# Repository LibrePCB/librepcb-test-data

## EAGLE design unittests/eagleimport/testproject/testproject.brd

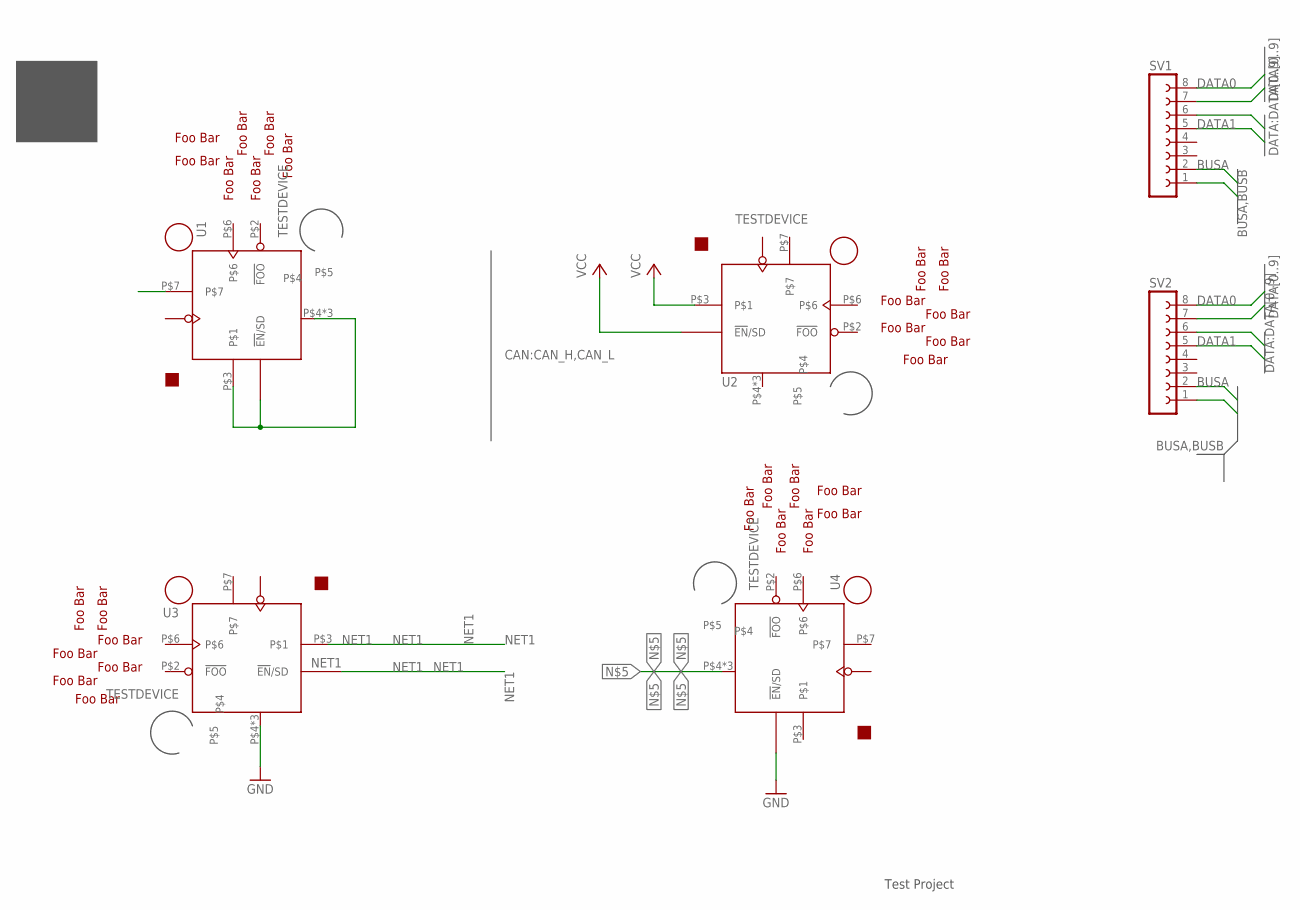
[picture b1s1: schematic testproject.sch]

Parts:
SV1, SV2: FE08-1; FE08
U1, U2, U3, U4: TESTDEVICE; TESTPACKAGE

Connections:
BUSA: SV1.2, SV2.2
BUSB: SV1.1, SV2.1
DATA0: SV1.6, SV1.8, SV2.6, SV2.8
DATA1: SV1.5, SV1.7, SV2.5, SV2.7
GND: U3.P$4, U3.P$13, U3.P$16, U4.P$1 (!EN!/SD)
unnamed: U1.P$1 (!EN!/SD), U1.P$3, U1.P$4, U1.P$13, U1.P$16
unnamed: U4.P$4, U4.P$13, U4.P$16
NET1: U3.P$1 (!EN!/SD), U3.P$3
VCC: U2.P$1 (!EN!/SD), U2.P$3

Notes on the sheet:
Test Project

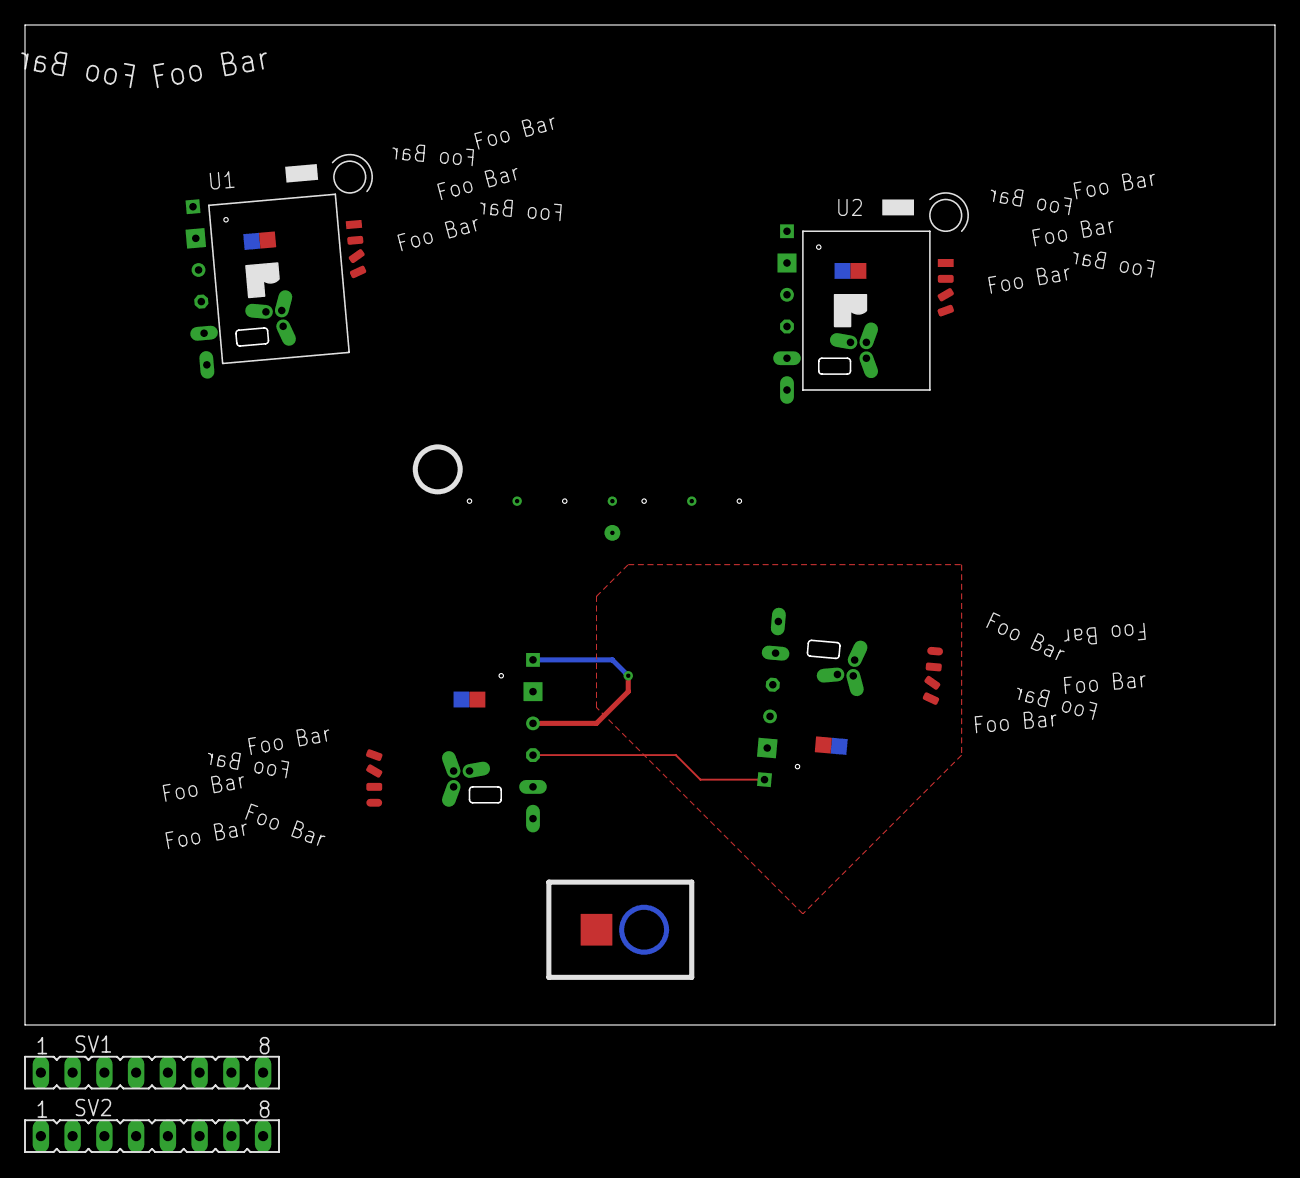
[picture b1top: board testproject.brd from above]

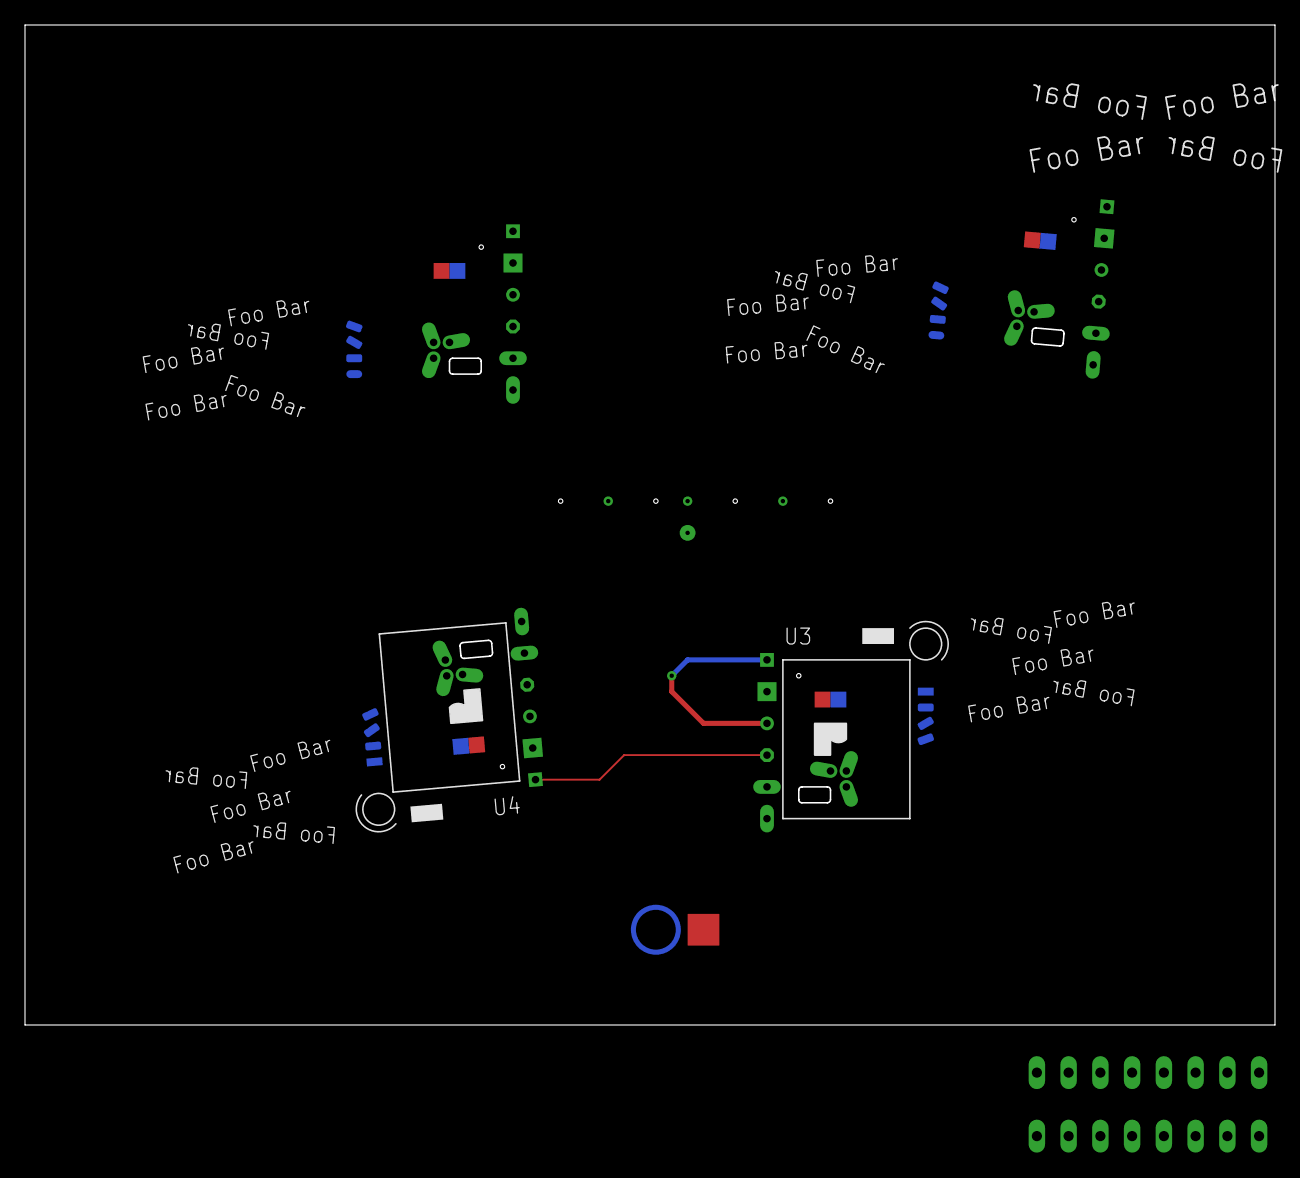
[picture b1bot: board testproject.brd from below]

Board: 2 copper layers, 100.0 x 80.0 mm, 6 parts (2 on the bottom side), 9 nets.

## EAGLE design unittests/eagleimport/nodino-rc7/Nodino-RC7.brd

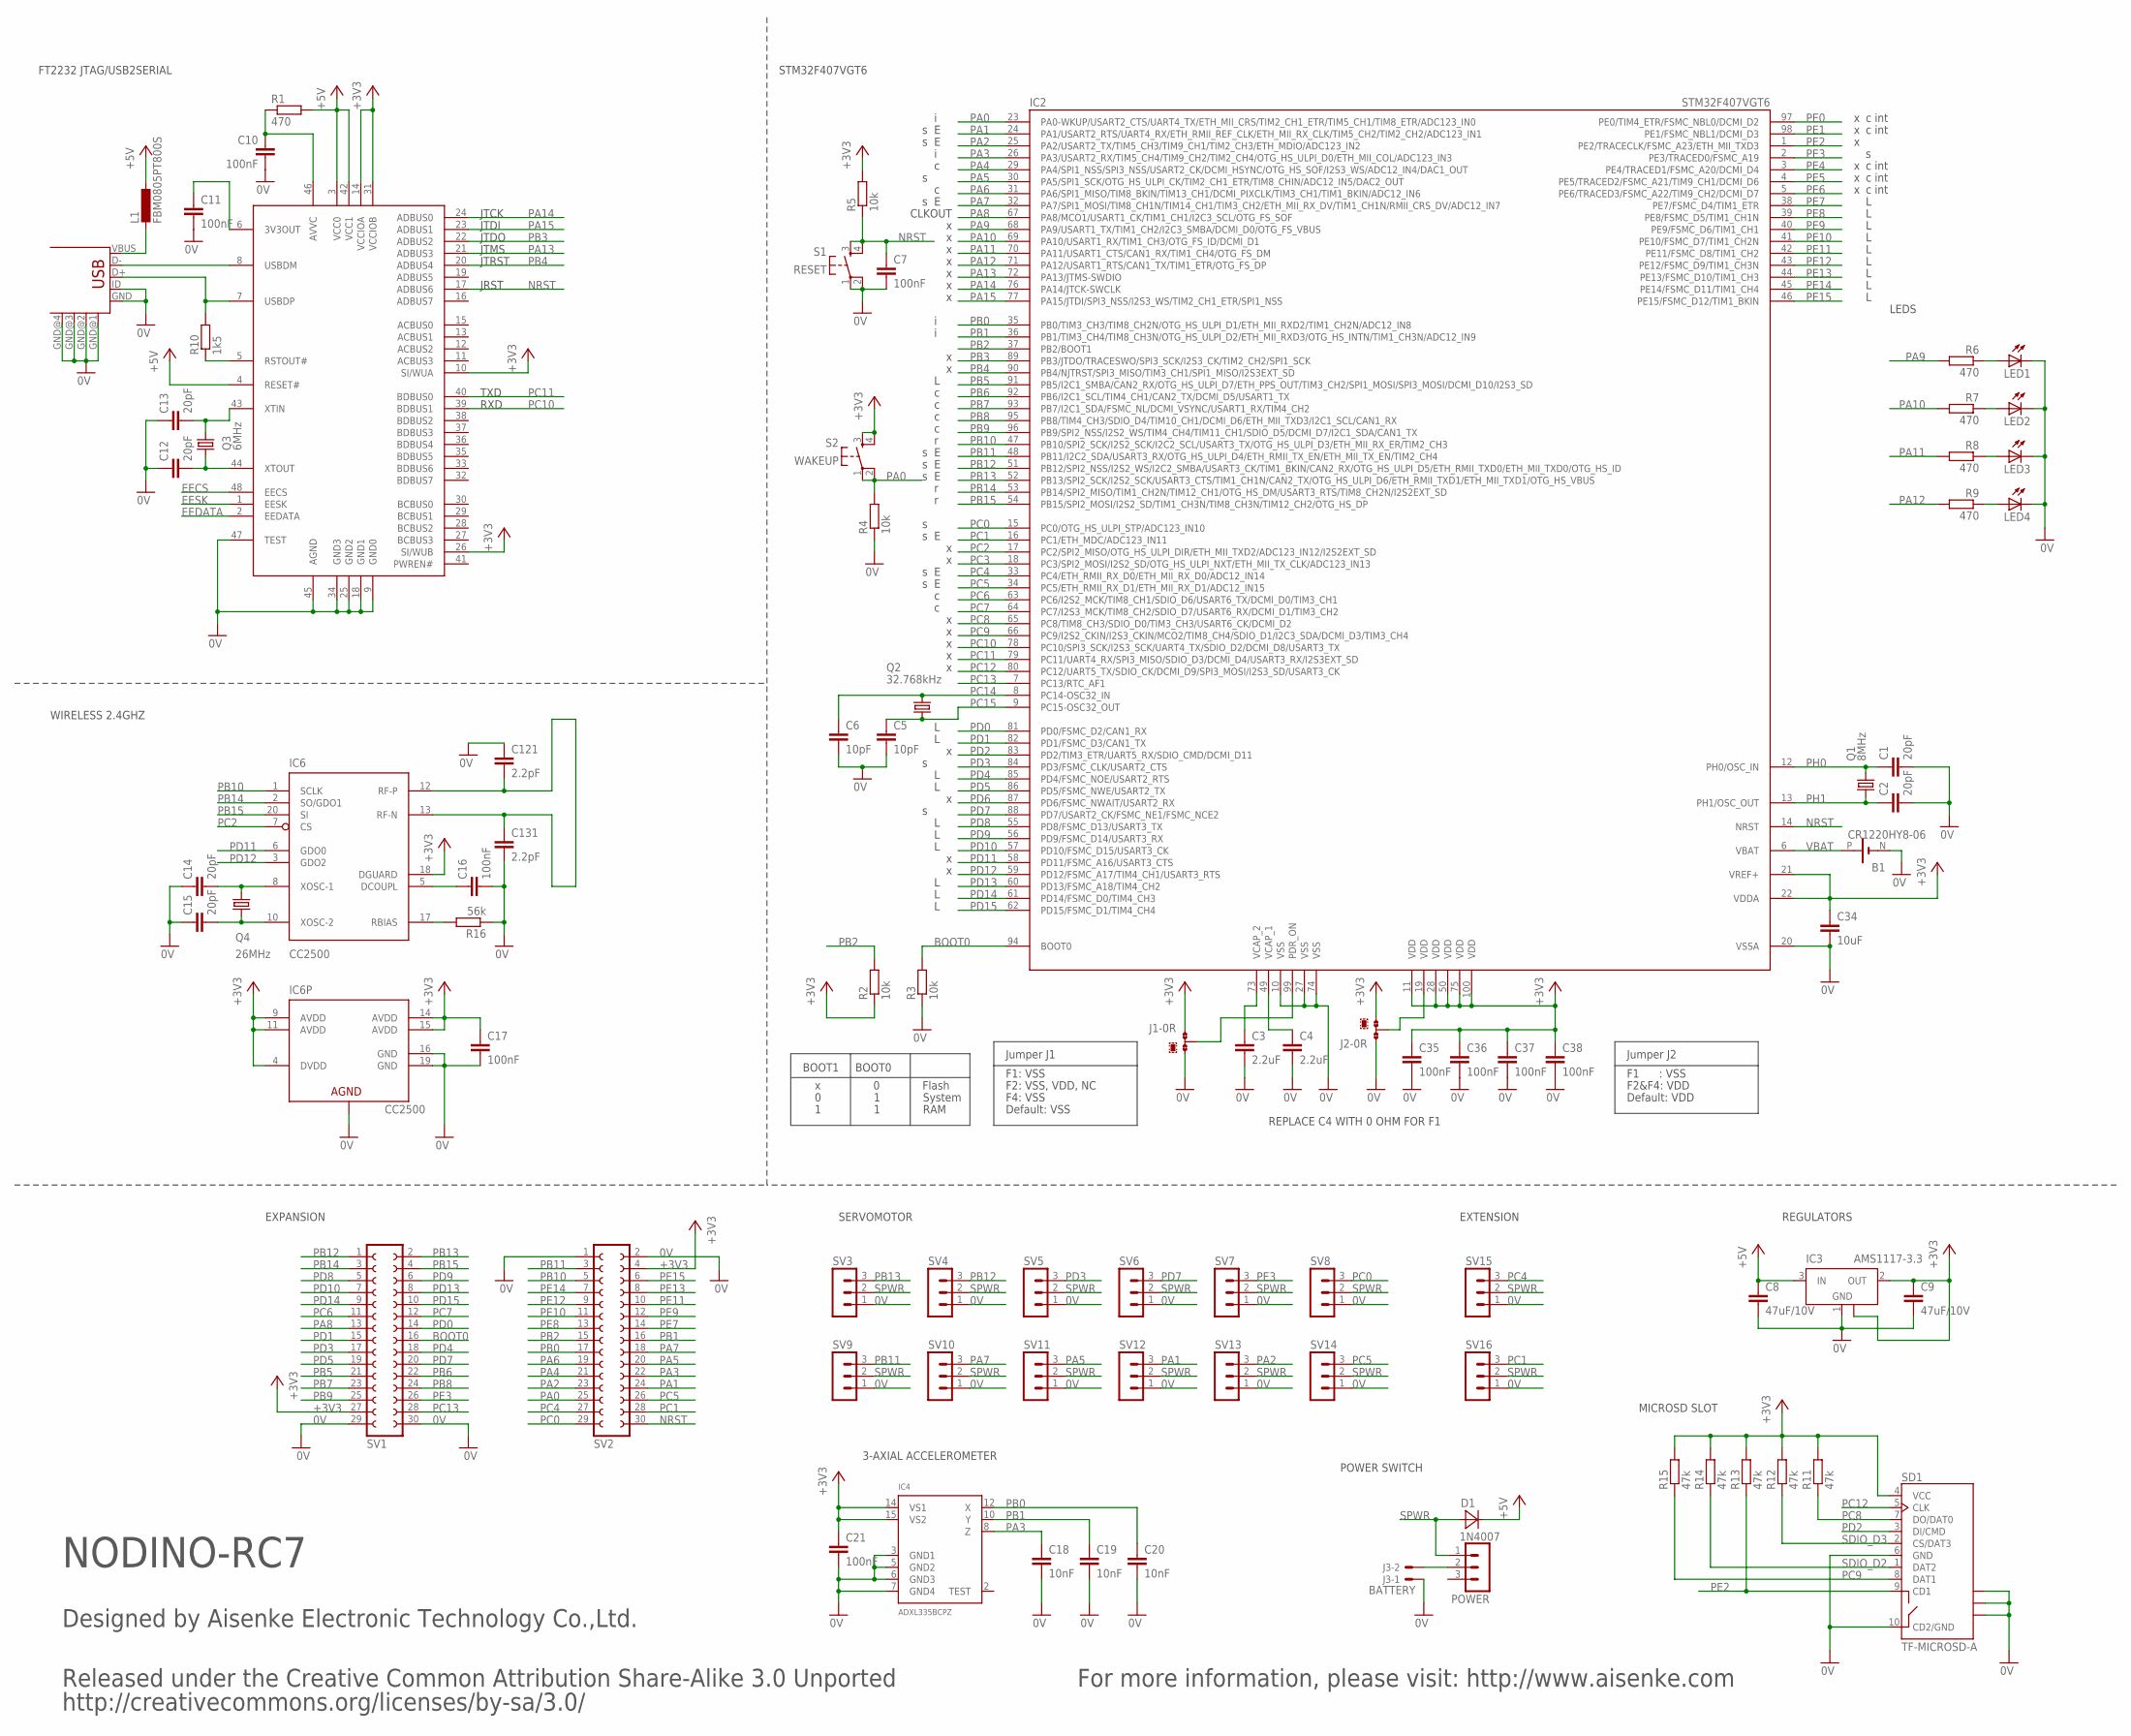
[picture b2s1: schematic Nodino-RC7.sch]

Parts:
B1: CR1220HY8-06; HY8-06
C1, C2, C12, C13, C14, C15: 20pF; C0603K
C3, C4: 2.2uF; C0603K
C5, C6: 10pF; C0603K
C7, C10, C11, C16, C17, C21, C35, C36, C37, C38: 100nF; C0603K
C8, C9: 47uF/10V; C3225
C18, C19, C20: 10nF; C0603K
C34: 10uF; C0603K
C121, C131: 2.2pF; C0603K
D1: 1N4007; DO214AC
IC1: FT2232D; LQFP48
IC2: STM32F407VGT6; LQFP100
IC3: AMS1117-3.3; SOT223
IC4: ADXL335BCPZ; LFCSP16-W
IC6: CC2500; QLP-20
J1, J2: 0R-JUMPA0603; A0R-JMP0603K
J3: BATTERY; 6410-02
L1: FBM0805PT800S; L0805
LED1, LED2, LED3, LED4: LEDCHIP-LED0805; CHIP-LED0805
POWER: MA03-1
Q1: 8MHz; CSM-7X-DU
Q2: 32.768kHz; MC-306
Q3: 6MHz; CSM-7X-DU
Q4: 26MHz; CSM-7X-DU
R1, R6, R7, R8, R9: 470; R0603K
R2, R3, R4, R5: 10k; R0603K
R10: 1k5; R0603K
R11, R12, R13, R14, R15: 47k; R0603K
R16: 56k; R0603K
S1: RESET; ALCOSWITCH-SMD
S2: WAKEUP; ALCOSWITCH-SMD
SD1: TF-MICROSD-A; MICROSD/CD
SV1, SV2: FE15-2
SV3, SV4, SV5, SV6, SV7, SV8, SV9, SV10, SV11, SV12, SV13, SV14, SV15, SV16: MA03-1
USB1: USB-SHIELD; USB-M-S1

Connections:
0V: B1.N (-), C1.2, C2.2, C3.2, C4.2, C5.2, C6.2, C7.2, C8.2, C9.2, C10.2, C11.2, C12.1, C13.1, C14.1, C15.1, C16.2, C17.2, C18.2, C19.2, C20.2, C21.2, C34.2, C35.2, C36.2, C37.2, C38.2, C121.1, C131.2, IC1.9 (GND0), IC1.18 (GND1), IC1.25 (GND2), IC1.34 (GND3), IC1.45 (AGND), IC1.47 (TEST), IC2.10 (VSS), IC2.20 (VSSA), IC2.27 (VSS), IC2.74 (VSS), IC3.1 (GND), IC4.3 (GND1), IC4.5 (GND2), IC4.6 (GND3), IC4.7 (GND4), IC6.16 (GND), IC6.19 (GND), IC6.21 (AGND), J1.1, J2.3, J3.1, LED1.C, LED2.C, LED3.C, LED4.C, R3.1, R4.1, R16.1, S1.1, S1.2 (P1), SD1.6 (GND), SD1.10 (CD2/GND), SD1.11 (GND), SD1.12 (GND), SD1.13 (GND), SV1.29, SV1.30, SV2.1, SV2.2, SV3.1, SV4.1, SV5.1, SV6.1, SV7.1, SV8.1, SV9.1, SV10.1, SV11.1, SV12.1, SV13.1, SV14.1, SV15.1, SV16.1, USB1.GND, USB1.GND@1 (GND), USB1.GND@2 (GND), USB1.GND@3 (GND), USB1.GND@4 (GND), USB1.ID
+3V3: C9.1, C17.1, C21.1, C34.1, C35.1, C36.1, C37.1, C38.1, IC1.10 (SI/WUA), IC1.14 (VCCIOA), IC1.26 (SI/WUB), IC1.31 (VCCIOB), IC2.11 (VDD), IC2.21 (VREF+), IC2.22 (VDDA), IC2.28 (VDD), IC2.50 (VDD), IC2.75 (VDD), IC2.100 (VDD), IC3.2 (OUT), IC3.4 (GND), IC4.14 (VS1), IC4.15 (VS2), IC6.4 (DVDD), IC6.9 (AVDD), IC6.11 (AVDD), IC6.14 (AVDD), IC6.15 (AVDD), IC6.18 (DGUARD), J1.3, J2.1, R2.1, R5.2, R11.2, R12.2, R13.2, R14.2, R15.2, S2.3 (S), S2.4 (S1), SD1.4 (VCC), SV1.27, SV2.4
+5V: C8.1, D1.C, IC1.3 (VCC0), IC1.4 (RESET#), IC1.42 (VCC1), IC3.3 (IN), L1.1, R1.2
BOOT0: IC2.94 (BOOT0), R3.2, SV1.16
DCOUPL: C16.1, IC6.5 (DCOUPL)
EECS: IC1.48 (EECS)
EEDATA: IC1.2 (EEDATA)
EESK: IC1.1 (EESK)
FOLDED_DIPOLE_ANTENNA: C121.2, C131.1, IC6.12 (RF-P), IC6.13 (RF-N)
unnamed: C15.2, IC6.10 (XOSC-2), Q4.1
unnamed: C3.1, IC2.73 (VCAP_2)
unnamed: C14.2, IC6.8 (XOSC-1), Q4.2
unnamed: C4.1, IC2.49 (VCAP_1)
unnamed: IC1.8 (USBDM), USB1.D-
unnamed: IC2.99 (PDR_ON), J1.2
unnamed: LED1.A, R6.1
unnamed: LED2.A, R7.1
unnamed: LED3.A, R8.1
unnamed: LED4.A, R9.1
unnamed: IC1.7 (USBDP), R10.2, USB1.D+
unnamed: L1.2, USB1.VBUS
unnamed: IC1.5 (RSTOUT#), R10.1
unnamed: C10.1, IC1.46 (AVVC), R1.1
unnamed: C11.1, IC1.6 (3V3OUT)
unnamed: C12.2, IC1.44 (XTOUT), Q3.1
unnamed: C13.2, IC1.43 (XTIN), Q3.2
unnamed: IC6.17 (RBIAS), R16.2
unnamed: IC2.19 (VDD), J2.2
unnamed: J3.2, POWER.2
NRST: C7.1, IC1.17 (ADBUS6), IC2.14 (NRST), R5.1, S1.3 (S), S1.4 (S1), SV2.30
PA0: IC2.23 (PA0-WKUP/USART2_CTS/UART4_TX/ETH_MII_CR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), R4.2, S2.1, S2.2 (P1), SV2.25
PA1: IC2.24 (PA1/USART2_RTS/UART4_RX/ETH_RMII_REF_CL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), SV2.24, SV12.3
PA2: IC2.25 (PA2/USART2_TX/TIM5_CH3/TIM9_CH1/TIM2_CH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), SV2.23, SV13.3
PA3: C18.1, IC2.26 (PA3/USART2_RX/TIM5_CH4/TIM9_CH2/TIM2_CH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), IC4.8 (Z), SV2.22
PA4: IC2.29 (PA4/SPI1_NSS/SPI3_NSS/USART2_CK/DCMI_HS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), SV2.21
PA5: IC2.30 (PA5/SPI1_SCK/OTG_HS_ULPI_CK/TIM2_CH1_ET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), SV2.20, SV11.3
PA6: IC2.31 (PA6/SPI1_MISO/TIM8_BKIN/TIM13_CH1/DCMI_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), SV2.19
PA7: IC2.32 (PA7/SPI1_MOSI/TIM8_CH1N/TIM14_CH1/TIM3_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), SV2.18, SV10.3
PA8: IC2.67 (PA8/MCO1/USART1_CK/TIM1_CH1/I2C3_SCL/OT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), SV1.13
PA9: IC2.68 (PA9/USART1_TX/TIM1_CH2/I2C3_SMBA/DCMI_D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), R6.2
PA10: IC2.69 (PA10/USART1_RX/TIM1_CH3/OTG_FS_ID/DCMI_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), R7.2
PA11: IC2.70 (PA11/USART1_CTS/CAN1_RX/TIM1_CH4/OTG_FS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), R8.2
PA12: IC2.71 (PA12/USART1_RTS/CAN1_TX/TIM1_ETR/OTG_FS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), R9.2
PA13: IC1.21 (ADBUS3), IC2.72 (PA13/JTMS-SWDIO)
PA14: IC1.24 (ADBUS0), IC2.76 (PA14/JTCK-SWCLK)
PA15: IC1.23 (ADBUS1), IC2.77 (PA15/JTDI/SPI3_NSS/I2S3_WS/TIM2_CH1_ETR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)
PB0: C20.1, IC2.35 (PB0/TIM3_CH3/TIM8_CH2N/OTG_HS_ULPI_D1/E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), IC4.12 (X), SV2.17
PB1: C19.1, IC2.36 (PB1/TIM3_CH4/TIM8_CH3N/OTG_HS_ULPI_D2/E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), IC4.10 (Y), SV2.16
PB2: IC2.37 (PB2/BOOT1), R2.2, SV2.15
PB3: IC1.22 (ADBUS2), IC2.89 (PB3/JTDO/TRACESWO/SPI3_SCK/I2S3_CK/TIM2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)
PB4: IC1.20 (ADBUS4), IC2.90 (PB4/NJTRST/SPI3_MISO/TIM3_CH1/SPI1_MISO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)
PB5: IC2.91 (PB5/I2C1_SMBA/CAN2_RX/OTG_HS_ULPI_D7/ET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), SV1.21
PB6: IC2.92 (PB6/I2C1_SCL/TIM4_CH1/CAN2_TX/DCMI_D5/U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), SV1.22
PB7: IC2.93 (PB7/I2C1_SDA/FSMC_NL/DCMI_VSYNC/USART1_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), SV1.23
PB8: IC2.95 (PB8/TIM4_CH3/SDIO_D4/TIM10_CH1/DCMI_D6/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), SV1.24
PB9: IC2.96 (PB9/SPI2_NSS/I2S2_WS/TIM4_CH4/TIM11_CH1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), SV1.25
PB10: IC2.47 (PB10/SPI2_SCK/I2S2_SCK/I2C2_SCL/USART3_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), IC6.1 (SCLK), SV2.5
PB11: IC2.48 (PB11/I2C2_SDA/USART3_RX/OTG_HS_ULPI_D4/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), SV2.3, SV9.3
PB12: IC2.51 (PB12/SPI2_NSS/I2S2_WS/I2C2_SMBA/USART3_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), SV1.1, SV4.3
PB13: IC2.52 (PB13/SPI2_SCK/I2S2_SCK/USART3_CTS/TIM1_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), SV1.2, SV3.3
PB14: IC2.53 (PB14/SPI2_MISO/TIM1_CH2N/TIM12_CH1/OTG_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), IC6.2 (SO/GDO1), SV1.3
PB15: IC2.54 (PB15/SPI2_MOSI/I2S2_SD/TIM1_CH3N/TIM8_C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), IC6.20 (SI), SV1.4
PC0: IC2.15 (PC0/OTG_HS_ULPI_STP/ADC123_IN10), SV2.29, SV8.3
PC1: IC2.16 (PC1/ETH_MDC/ADC123_IN11), SV2.28, SV16.3
PC2: IC2.17 (PC2/SPI2_MISO/OTG_HS_ULPI_DIR/ETH_MII_T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), IC6.7 (CS)
PC3: IC2.18 (PC3/SPI2_MOSI/I2S2_SD/OTG_HS_ULPI_NXT/E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)
PC4: IC2.33 (PC4/ETH_RMII_RX_D0/ETH_MII_RX_D0/ADC12_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), SV2.27, SV15.3
PC5: IC2.34 (PC5/ETH_RMII_RX_D1/ETH_MII_RX_D1/ADC12_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), SV2.26, SV14.3
PC6: IC2.63 (PC6/I2S2_MCK/TIM8_CH1/SDIO_D6/USART6_TX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), SV1.11
PC7: IC2.64 (PC7/I2S3_MCK/TIM8_CH2/SDIO_D7/USART6_RX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), SV1.12
PC8: IC2.65 (PC8/TIM8_CH3/SDIO_D0/TIM3_CH3/USART6_CK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), R11.1, SD1.7 (DO/DAT0)
PC9: IC2.66 (PC9/I2S2_CKIN/I2S3_CKIN/MCO2/TIM8_CH4/S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), R15.1, SD1.8 (DAT1)
PC10: IC1.39 (BDBUS1), IC2.78 (PC10/SPI3_SCK/I2S3_SCK/UART4_TX/SDIO_D2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)
PC11: IC1.40 (BDBUS0), IC2.79 (PC11/UART4_RX/SPI3_MISO/SDIO_D3/DCMI_D4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)
PC12: IC2.80 (PC12/UART5_TX/SDIO_CK/DCMI_D9/SPI3_MOSI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), SD1.5 (CLK)
PC13: IC2.7 (PC13/RTC_AF1), SV1.28
PC14: C6.1, IC2.8 (PC14-OSC32_IN), Q2.4 (2)
PC15: C5.1, IC2.9 (PC15-OSC32_OUT), Q2.1
PD0: IC2.81 (PD0/FSMC_D2/CAN1_RX), SV1.14
PD1: IC2.82 (PD1/FSMC_D3/CAN1_TX), SV1.15
PD2: IC2.83 (PD2/TIM3_ETR/UART5_RX/SDIO_CMD/DCMI_D11), SD1.3 (DI/CMD)
PD3: IC2.84 (PD3/FSMC_CLK/USART2_CTS), SV1.17, SV5.3
PD4: IC2.85 (PD4/FSMC_NOE/USART2_RTS), SV1.18
PD5: IC2.86 (PD5/FSMC_NWE/USART2_TX), SV1.19
PD6: IC2.87 (PD6/FSMC_NWAIT/USART2_RX)
PD7: IC2.88 (PD7/USART2_CK/FSMC_NE1/FSMC_NCE2), SV1.20, SV6.3
PD8: IC2.55 (PD8/FSMC_D13/USART3_TX), SV1.5
PD9: IC2.56 (PD9/FSMC_D14/USART3_RX), SV1.6
PD10: IC2.57 (PD10/FSMC_D15/USART3_CK), SV1.7
PD11: IC2.58 (PD11/FSMC_A16/USART3_CTS), IC6.6 (GDO0)
PD12: IC2.59 (PD12/FSMC_A17/TIM4_CH1/USART3_RTS), IC6.3 (GDO2)
PD13: IC2.60 (PD13/FSMC_A18/TIM4_CH2), SV1.8
PD14: IC2.61 (PD14/FSMC_D0/TIM4_CH3), SV1.9
PD15: IC2.62 (PD15/FSMC_D1/TIM4_CH4), SV1.10
PE0: IC2.97 (PE0/TIM4_ETR/FSMC_NBL0/DCMI_D2)
PE1: IC2.98 (PE1/FSMC_NBL1/DCMI_D3)
PE2: IC2.1 (PE2/TRACECLK/FSMC_A23/ETH_MII_TXD3), R13.1, SD1.9 (CD1)
PE3: IC2.2 (PE3/TRACED0/FSMC_A19), SV1.26, SV7.3
PE4: IC2.3 (PE4/TRACED1/FSMC_A20/DCMI_D4)
PE5: IC2.4 (PE5/TRACED2/FSMC_A21/TIM9_CH1/DCMI_D6)
PE6: IC2.5 (PE6/TRACED3/FSMC_A22/TIM9_CH2/DCMI_D7)
PE7: IC2.38 (PE7/FSMC_D4/TIM1_ETR), SV2.14
PE8: IC2.39 (PE8/FSMC_D5/TIM1_CH1N), SV2.13
PE9: IC2.40 (PE9/FSMC_D6/TIM1_CH1), SV2.12
PE10: IC2.41 (PE10/FSMC_D7/TIM1_CH2N), SV2.11
PE11: IC2.42 (PE11/FSMC_D8/TIM1_CH2), SV2.10
PE12: IC2.43 (PE12/FSMC_D9/TIM1_CH3N), SV2.9
PE13: IC2.44 (PE13/FSMC_D10/TIM1_CH3), SV2.8
PE14: IC2.45 (PE14/FSMC_D11/TIM1_CH4), SV2.7
PE15: IC2.46 (PE15/FSMC_D12/TIM1_BKIN), SV2.6
PH0: C1.1, IC2.12 (PH0/OSC_IN), Q1.2
PH1: C2.1, IC2.13 (PH1/OSC_OUT), Q1.1
SDIO_D2: R14.1, SD1.1 (DAT2)
SDIO_D3: R12.1, SD1.2 (CS/DAT3)
SPWR: D1.A, POWER.1, SV3.2, SV4.2, SV5.2, SV6.2, SV7.2, SV8.2, SV9.2, SV10.2, SV11.2, SV12.2, SV13.2, SV14.2, SV15.2, SV16.2
VBAT: B1.P (+), IC2.6 (VBAT)

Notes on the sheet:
F2: VSS, VDD, NC
F4: VSS
BOOT1 BOOT0
x 0 Flash
0 1 System
1 1 RAM
Default: VSS
STM32F407VGT6
FT2232 JTAG/USB2SERIAL
REGULATORS
MICROSD SLOT
LEDS
NODINO-RC7
Designed by Aisenke Electronic Technology Co.,Ltd.
Released under the Creative Common Attribution Share-Alike 3.0 Unported
http://creativecommons.org/licenses/by-sa/3.0/
For more information, please visit: http://www.aisenke.com
Jumper J1
RXD
TXD
JRST
JTRST
JTMS
JTDO
JTDI
JTCK
F1 : VSS
F2&F4: VDD
Default: VDD
Jumper J2
F1: VSS
REPLACE C4 WITH 0 OHM FOR F1
WIRELESS 2.4GHZ
EXPANSION
3-AXIAL ACCELEROMETER
c int
CLKOUT
SERVOMOTOR
EXTENSION
POWER SWITCH

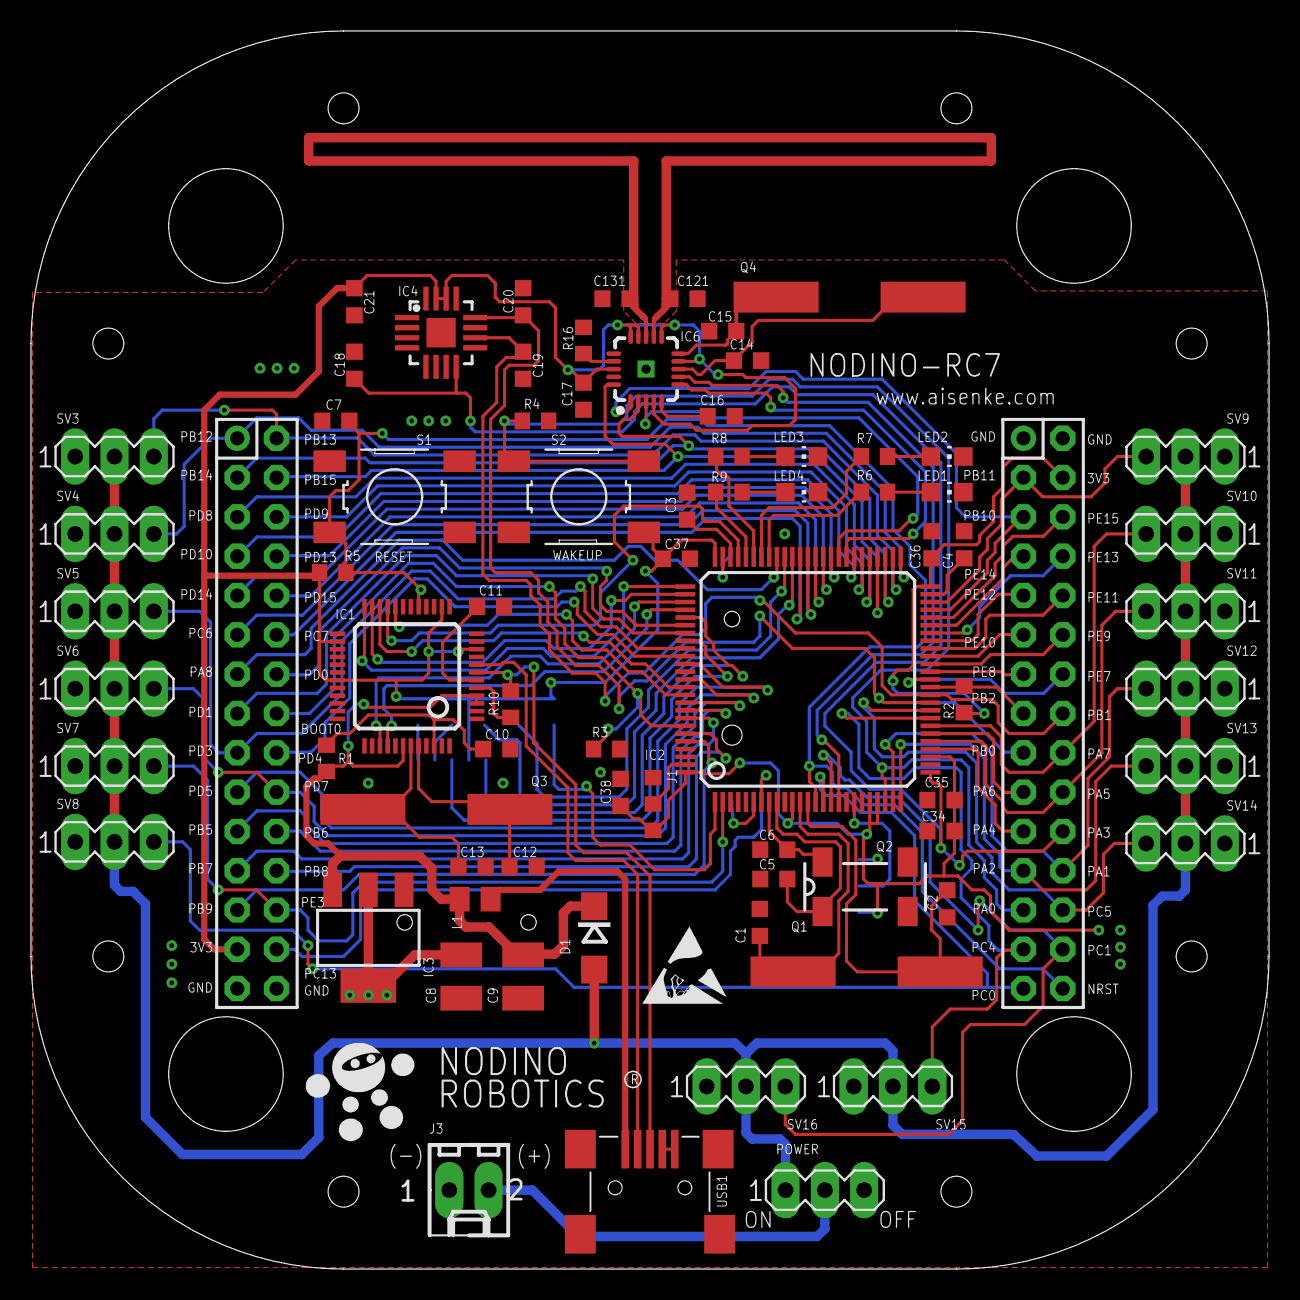
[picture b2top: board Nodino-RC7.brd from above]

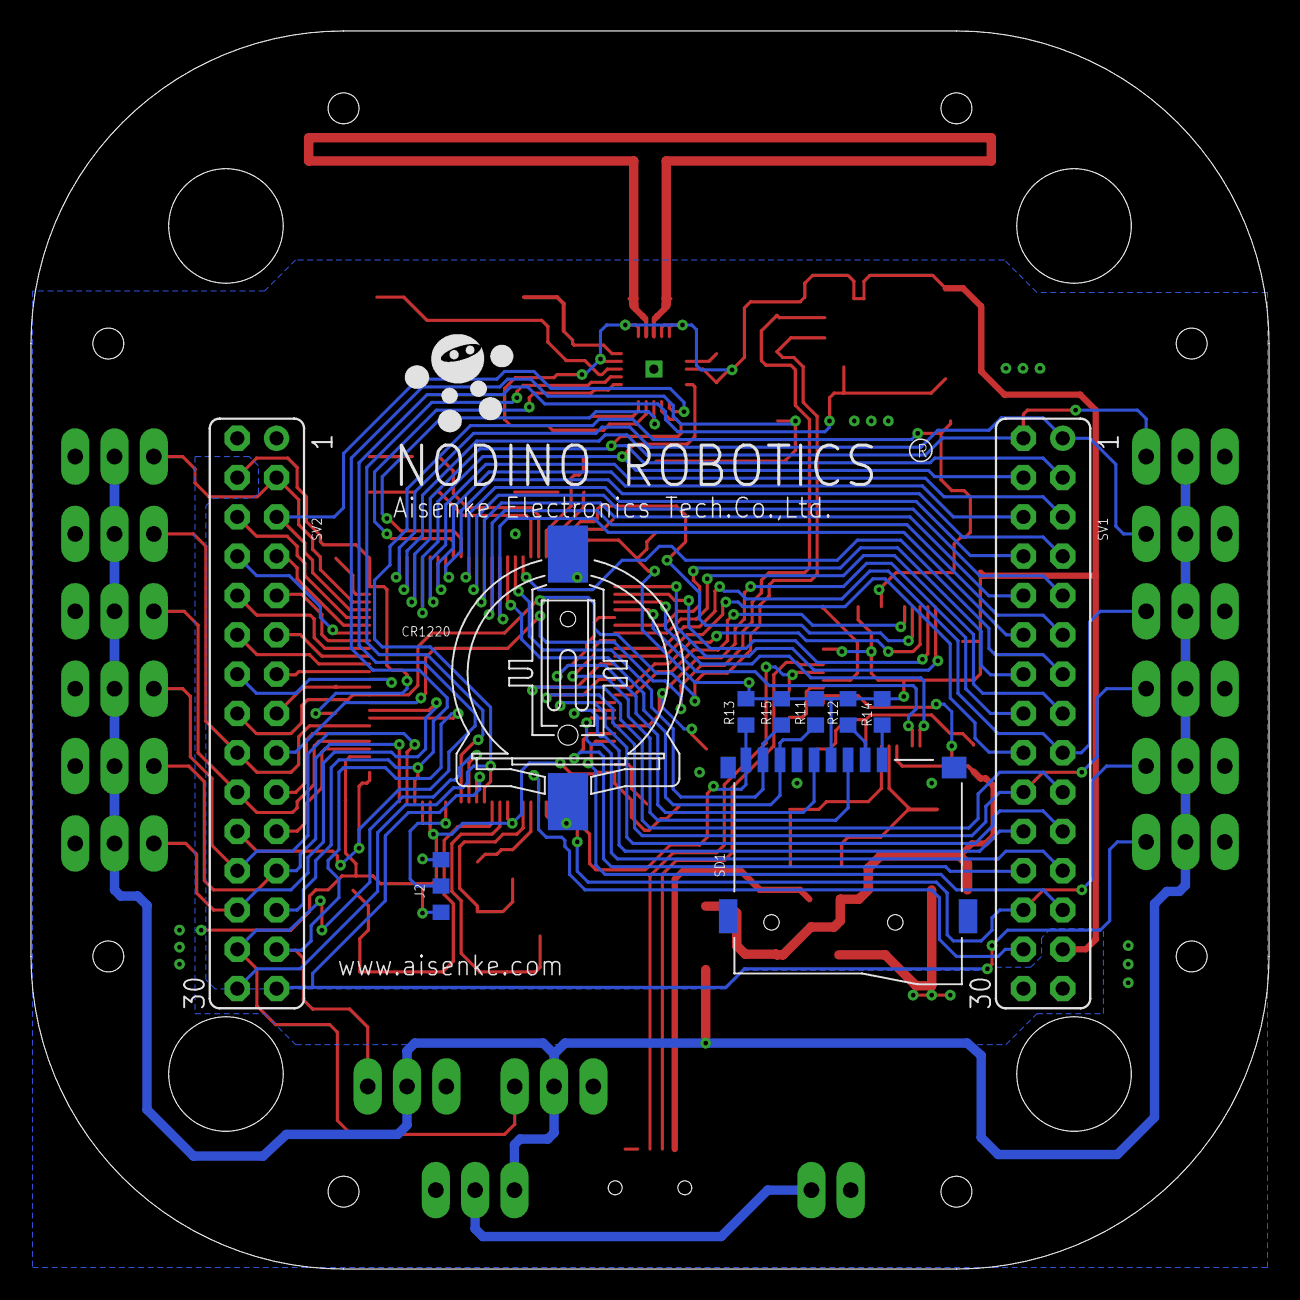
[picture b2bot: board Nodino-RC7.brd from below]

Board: 2 copper layers, 80.0 x 80.0 mm, 84 parts (10 on the bottom side), 106 nets.

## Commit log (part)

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2017-08-20 Add common/api/v1/libraries
    Downloaded from https://api.librepcb.org/api/v1/libraries
2017-08-20 Add unit/FileDownloadTest/first_pcb.zip
    Downloaded from
    https://github.com/LibrePCB/LibrePCB/archive/first_pcb.zip
2017-10-15 Add files for "eagleimport" tests
2018-05-05 Add files for BoardPlaneFragmentsBuilderTest
2018-06-16 Upgrade test projects to new file format
2018-07-07 Tidy up folder structure
2018-09-18 Add CLI test data
2018-09-23 Add files for funq fixtures
2018-10-07 Add populated library for functional tests
2018-10-12 Update URL to website (http -> https)
    Our website now supports TLS, so all URLs should be changed from
    http://librepcb.org to https://librepcb.org.
2019-02-24 Update to latest file format
2019-08-28 Refactor directory structure
2019-08-29 Add demo library elements
2019-09-02 Add data for BoardGerberExportTest
2019-12-24 Add data for BoardPickPlaceGeneratorTest
2020-01-03 Add helper script to update file format
2020-01-03 Update file format
2021-03-09 Update file format of schematic netlabels
2021-03-14 Update generated Gerber files
2021-04-02 Update generated Gerber/Excellon files
2021-07-11 Update generated Gerber/Excellon files
    (cherry picked from commit dc902dcdaf51105ecd10e1fb14cb0f8e0442bf8f)
2022-02-20 BoardPlaneFragmentsBuilderTest: Make output deterministic
2022-03-11 Update generated plane fragments
2022-03-26 Update project files
2022-04-22 Update symbols
2022-05-19 Rename workspace directory "v0.2" to "data"
2022-09-08 Add data for Gerber X3 assembly export test
2022-09-23 BoardPlaneFragmentsBuilderTest: Make output deterministic
    (cherry picked from commit b2fcf5640d6d52cb8ac651894343def28b178ab0)
2022-09-23 Update generated Gerber/Excellon files
    (cherry picked from commit 9aef98dd8b48944e8e4fa498e0f6ff08cd820a8d)
2022-09-23 Update generated Gerber files
    (cherry picked from commit 75677625c594d20703dfca207d6ce7ed53a38a0b)
2022-09-23 Update generated plane fragments
    (cherry picked from commit 9a1e9fffaa6acca7f8635b1ccd6e005e1fd7dd0e)
2022-09-23 Add data for Gerber X3 assembly export test
    (cherry picked from commit e6a2215b101b10b6612d747d53ce385cd8fc3936)
2022-12-10 Update file format of fabrication output settings
2022-12-10 Update file format of holes
2022-12-19 Update file format of pads
2023-01-14 Update file format of schematics
2023-01-24 Update generated Gerber files & plane fragments
2023-01-25 Update file format of grid settings
2023-01-26 Update boards, generated Gerber files & plane fragments
2023-01-30 Set LIBREPCB_UPGRADE_UNSTABLE=1 in update_file_format.py
    To upgrade the unstable file format.
2023-01-30 Update file format of boards
2023-02-17 Update file format of packages
2023-03-06 Update file format of ERC/DRC approvals
2023-03-06 Add test file for IPC-D-356A netlist export
    (cherry picked from commit 060409082bf9095c0b6df8741d0d08460171a759)
2023-03-09 Update pick&place files
2023-03-09 Update pick&place files
    (cherry picked from commit b5f4ceb5321fedc445b52c0f3b37feade385675f)
2023-03-15 Add test file for IPC-D-356A netlist export
2023-03-16 Update file format of project settings
2023-04-06 Update file format of packages and boards
2023-05-01 Update file format of workspace settings
2023-05-04 Update generated test data
2023-05-05 Update generated files
2023-05-08 Add test data for OccModelTest
2023-05-08 Add STEP model to a package
2023-05-08 Update file format of packages & boards
2023-07-11 Upgrade file format of libraries
2023-07-20 Update file format of projects
2023-08-04 Upgrade file format of projects
2023-08-10 Update file format of libraries
2023-08-18 Use more features in files
2023-08-18 Add test data with file format v0.1
2023-08-18 Upgrade file format to v1
2024-01-22 Add EAGLE project files
2024-03-20 Add STEP model for color test
2024-04-01 Add more Eagle test projects
2024-10-27 Gerber Test: Add more features to board
2024-10-27 Add test data for Specctra export/import
2024-11-08 Add test data for DRC tests
2024-11-24 Add test data for KiCad library import
2024-12-25 Fix STEP files crashing OpenCascade
2025-01-16 Add test data for interactive HTML BOM
2025-01-25 Approve DRC messages for new via DRC checks
2025-01-26 Add test data for useless via DRC check
2025-03-07 Add KiCad v6 test files
2025-06-18 Fix missing default names in libraries API
2025-07-02 Update RESC2012 (0805) package
2025-08-05 Add copies for v1 file format
2025-08-05 Upgrade all files to v2
2025-08-08 Add board rendering output job to project
2025-08-08 update_file_format.py: Skip versioned directories
2025-08-08 Add grid_interval to symbols & packages
2025-08-14 Add images to a symbol and project
2025-08-19 Update boards with new DRC approvals
2025-08-22 Add more test data to libraries & projects
2025-08-22 Add glue flag to board devices
2025-08-23 Add lock property to symbol/schematic texts
2025-08-25 Make netline anchors canonical
2025-09-04 Add board pads to test projects
2025-09-05 Add board pads to DRC test project
2025-09-16 Update workspace settings
2025-09-22 Update file format of vias
2025-09-22 Add vias with auto-size to test projects
2025-09-23 Add i18n test files
2025-09-23 Upgrade file format of planes
2025-09-23 Use individual plane clearances in projects
2025-10-01 Upgrade file format of design rules & net classes
2025-10-02 Use vias with automatic drill in projects
2025-10-02 Upgrade file format of net classes
2025-10-02 Use custom net class design rules in test projects
2025-10-03 Upgrade file format of packages
2025-10-22 Use plated cutouts in test projects
2025-11-03 Upgrade file format of DRC settings
2025-11-04 Add corporates to populated library
2025-11-07 Add lock attribute to footprint stroke texts
2025-11-18 Add organizations to populated library
2025-12-12 Add buses to a project
2025-12-25 Add DRC test case for impossible pad connections
2026-01-03 Upgrade file format of packages & boards
2026-01-11 Upgrade file format of devices
2026-02-07 Add DRC test case for too thin plane thermal spokes
2026-03-19 Update translations
2026-03-26 Add cmpcat with endless recursion
2026-04-17 Add buses to Eagle test project
2026-04-18 Move Eagle testproject.sch/brd into subdirectory
2026-04-18 Add golden sample for Eagle project import
2026-04-18 Add update_golden_samples.sh
2026-04-26 Disable automatic library updates
2026-05-12 Add expected.json for IBOM test
2026-05-12 Update golden sample of IBOM test
2026-05-14 Add DRC test case for board outline intersections
2026-06-06 Add SES test file from FreeRouting 2.4.0
